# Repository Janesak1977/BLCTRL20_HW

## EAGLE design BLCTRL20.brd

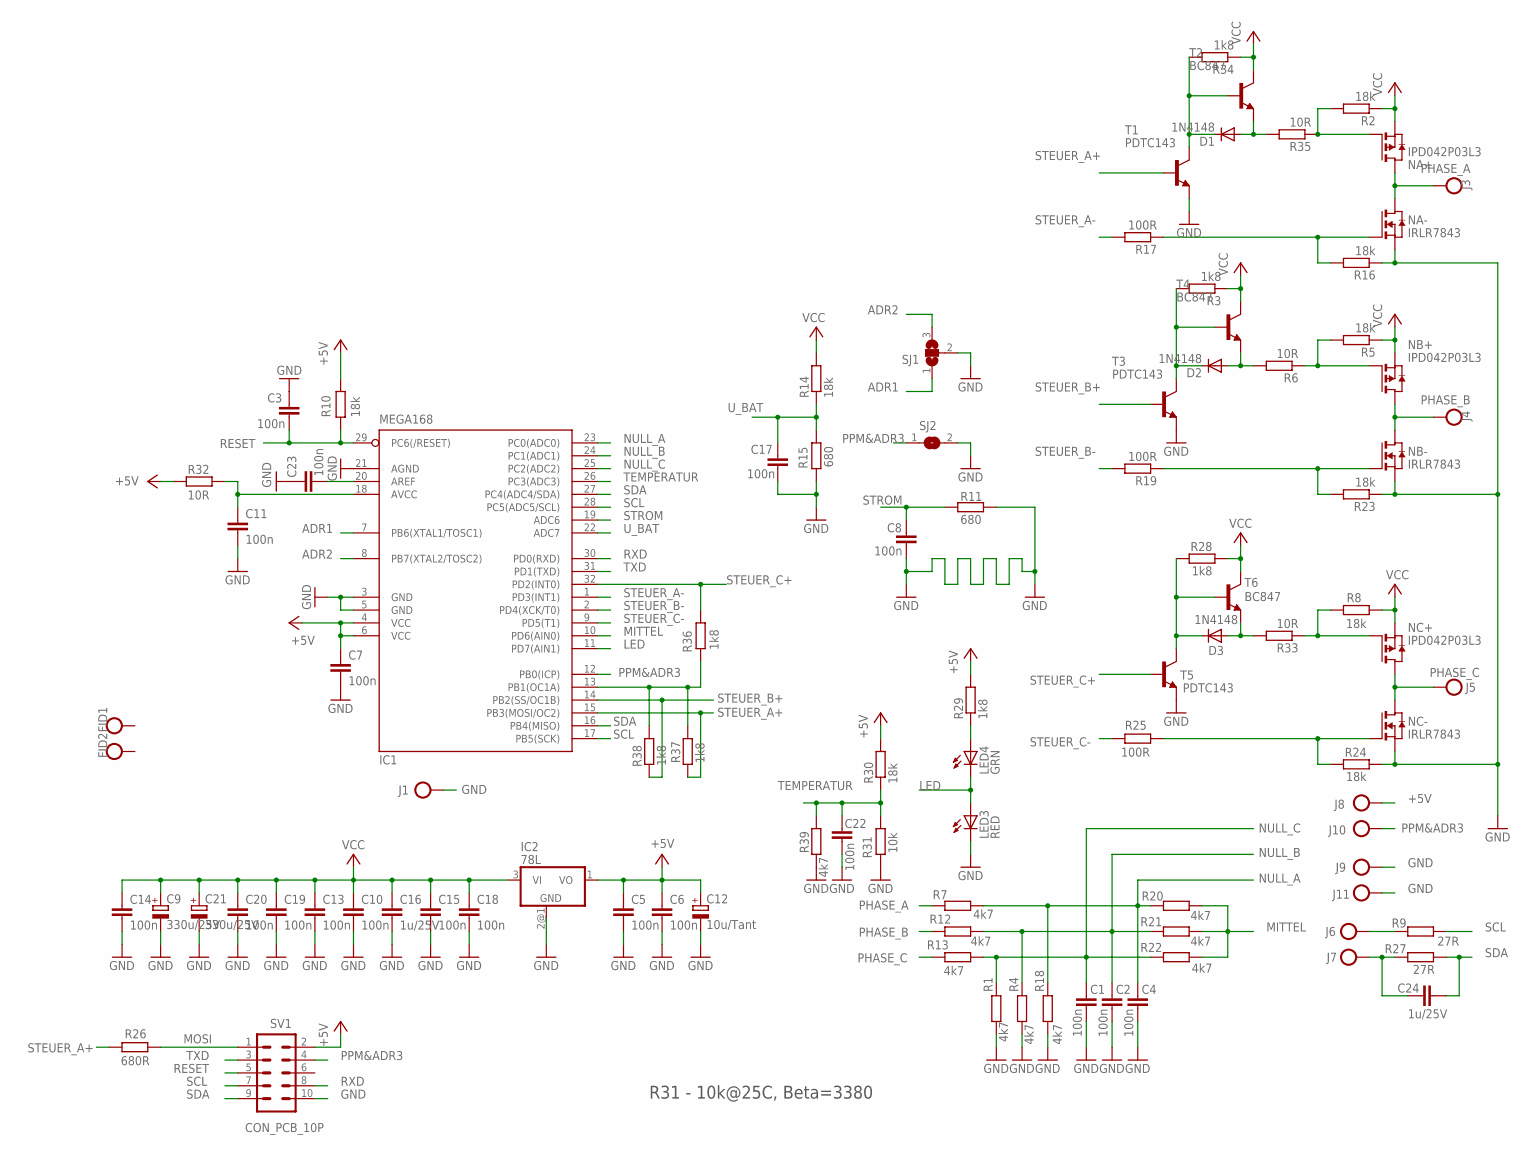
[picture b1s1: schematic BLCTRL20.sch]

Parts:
C1, C2, C3, C4, C5, C6, C7, C8, C10, C11, C13, C14, C15, C17, C18, C19, C20, C22, C23: 100n; C0603
C9, C21: 330u/25V; E2,5-5
C12: 10u/Tant; PANASONIC_B
C16, C24: 1u/25V; C0603
D1, D2, D3: 1N4148; SOD323-W
FID1, FID2: FIDUCIAL; FIDUCIAL_MARK
IC1: MEGA168; TQFP32-08
IC2: 78L; SOT89
J1, J3, J4, J5: SMDPAD40X20; PAD40X20
J6, J7: SE11
J8, J9, J10: SMDPAD25X25; PAD24X15
J11: SMDPAD24X12; PAD24X12
LED3: RED; CHIPLED_0603
LED4: GRN; CHIPLED_0603
NA+: IPD042P03L3; TO252
NA-: IRLR7843; TO252
NB+: IPD042P03L3; TO252
NB-: IRLR7843; TO252
NC+: IPD042P03L3; TO252
NC-: IRLR7843; TO252
R1, R4, R7, R12, R13, R18, R20, R21, R22, R39: 4k7; R0603
R2, R5, R8, R16, R23, R24: 18k; R0805
R3, R28, R29, R34, R36, R37, R38: 1k8; R0603
R6, R32, R33, R35: 10R; R0603
R9, R27: 27R; R0603
R10, R14, R30: 18k; R0603
R11, R15: 680; R0603
R17, R19, R25: 100R; R0603
R26: 680R; R0603
R31: 10k; R0603
SJ1: SJ2W; SJ_2
SJ2: SJ
SV1: CON_PCB_10P; BOARD_CON_SMD
T1, T3, T5: PDTC143; SC75_INFINEON
T2, T4, T6: BC847; SC75_INFINEON

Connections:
+5V: C5.1, C6.1, C7.1, C12.+, IC1.4 (VCC), IC1.6 (VCC), IC2.1 (VO), J8.P$1, R10.2, R29.2, R30.2, R32.2, SV1.2
ADR1: IC1.7 (PB6(XTAL1/TOSC1)), SJ1.1
ADR2: IC1.8 (PB7(XTAL2/TOSC2)), SJ1.3
GND: C1.2, C2.2, C3.1, C4.2, C5.2, C6.2, C7.2, C8.2, C9.-, C10.2, C11.2, C12.-, C13.2, C14.2, C15.2, C16.2, C17.2, C18.2, C19.2, C20.2, C21.-, C22.2, C23.1, IC1.3 (GND), IC1.5 (GND), IC1.21 (AGND), IC2.2@1 (GND), J1.P$1, J9.P$1, J11.P$1, LED3.C, NA-.3 (S), NB-.3 (S), NC-.3 (S), R1.1, R4.1, R11.1, R15.1, R16.1, R18.1, R23.1, R24.1, R31.1, R39.1, SJ1.2, SJ2.2, SV1.10, T1.2 (E), T3.2 (E), T5.2 (E)
LED: IC1.11 (PD7(AIN1)), LED3.A, LED4.C
MITTEL: IC1.10 (PD6(AIN0)), R20.1, R21.1, R22.1
MOSI: R26.1, SV1.1
unnamed: LED4.A, R29.1
unnamed: NA-.1 (G), R16.2, R17.1
unnamed: NA+.1 (G), R2.2, R35.1
unnamed: D1.A, R35.2, T2.2 (E)
unnamed: D1.C, R34.2, T1.3 (C), T2.1 (B)
unnamed: C24.2, J7.MP, R27.2
unnamed: J6.MP, R9.2
unnamed: NC-.1 (G), R24.2, R25.1
unnamed: NB-.1 (G), R19.1, R23.2
unnamed: NC+.1 (G), R8.2, R33.1
unnamed: NB+.1 (G), R5.2, R6.1
unnamed: D2.A, R6.2, T4.2 (E)
unnamed: D3.A, R33.2, T6.2 (E)
unnamed: D2.C, R3.2, T3.3 (C), T4.1 (B)
unnamed: D3.C, R28.2, T5.3 (C), T6.1 (B)
unnamed: IC1.13 (PB1(OC1A)), R36.1, R37.2, R38.2
unnamed: C23.2, IC1.20 (AREF)
unnamed: C11.1, IC1.18 (AVCC), R32.1
NULL_A: C4.1, IC1.23 (PC0(ADC0)), R7.1, R18.2, R20.2
NULL_B: C2.1, IC1.24 (PC1(ADC1)), R4.2, R12.1, R21.2
NULL_C: C1.1, IC1.25 (PC2(ADC2)), R1.2, R13.1, R22.2
PHASE_A: J3.P$1, NA+.2 (D), NA-.2 (D), R7.2
PHASE_B: J4.P$1, NB+.2 (D), NB-.2 (D), R12.2
PHASE_C: J5.P$1, NC+.2 (D), NC-.2 (D), R13.2
PPM&ADR3: IC1.12 (PB0(ICP)), J10.P$1, SJ2.1, SV1.4
RESET: C3.2, IC1.29 (PC6(/RESET)), R10.1, SV1.5
RXD: IC1.30 (PD0(RXD)), SV1.8
SCL: IC1.17 (PB5(SCK)), IC1.28 (PC5(ADC5/SCL)), R9.1, SV1.7
SDA: C24.1, IC1.16 (PB4(MISO)), IC1.27 (PC4(ADC4/SDA)), R27.1, SV1.9
STEUER_A+: IC1.15 (PB3(MOSI/OC2)), R26.2, R37.1, T1.1 (B)
STEUER_A-: IC1.1 (PD3(INT1)), R17.2
STEUER_B+: IC1.14 (PB2(SS/OC1B)), R38.1, T3.1 (B)
STEUER_B-: IC1.2 (PD4(XCK/T0)), R19.2
STEUER_C+: IC1.32 (PD2(INT0)), R36.2, T5.1 (B)
STEUER_C-: IC1.9 (PD5(T1)), R25.2
STROM: C8.1, IC1.19 (ADC6), R11.2
TEMPERATUR: C22.1, IC1.26 (PC3(ADC3)), R30.1, R31.2, R39.2
TXD: IC1.31 (PD1(TXD)), SV1.3
U_BAT: C17.1, IC1.22 (ADC7), R14.1, R15.2
VCC: C9.+, C10.1, C13.1, C14.1, C15.1, C16.1, C18.1, C19.1, C20.1, C21.+, IC2.3 (VI), NA+.3 (S), NB+.3 (S), NC+.3 (S), R2.1, R3.1, R5.1, R8.1, R14.2, R28.1, R34.1, T2.3 (C), T4.3 (C), T6.3 (C)

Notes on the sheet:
R31 - 10k@25C, Beta=3380

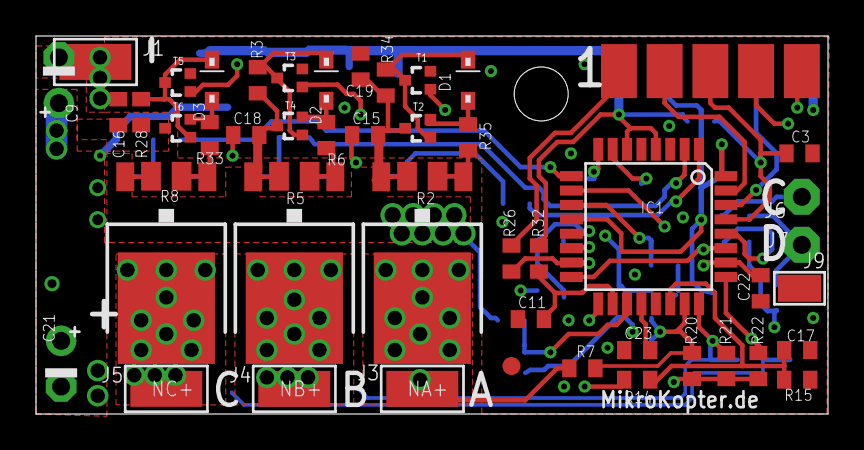
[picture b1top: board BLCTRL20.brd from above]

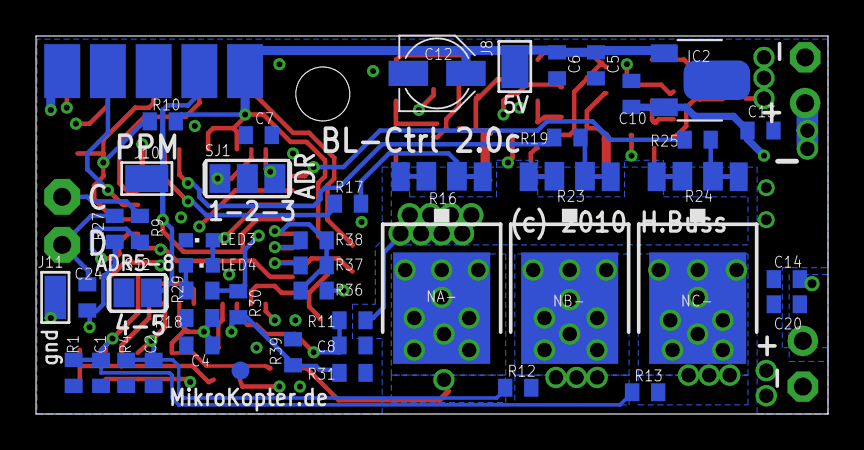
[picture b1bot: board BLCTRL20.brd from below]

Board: 4 copper layers, 44.0 x 21.0 mm, 97 parts (47 on the bottom side), 47 nets.

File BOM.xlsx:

Part | Value | Device | Package
R11 | 680 | R-EU_R0603 | R0603
R15 | 680 | R-EU_R0603 | R0603
C1 | 100n | C-EUC0603 | C0603
C10 | 100n | C-EUC0603 | C0603
C11 | 100n | C-EUC0603 | C0603
C13 | 100n | C-EUC0603 | C0603
C14 | 100n | C-EUC0603 | C0603
C15 | 100n | C-EUC0603 | C0603
C17 | 100n | C-EUC0603 | C0603
C18 | 100n | C-EUC0603 | C0603
C19 | 100n | C-EUC0603 | C0603
C2 | 100n | C-EUC0603 | C0603
C20 | 100n | C-EUC0603 | C0603
C22 | 100n | C-EUC0603 | C0603
C23 | 100n | C-EUC0603 | C0603
C3 | 100n | C-EUC0603 | C0603
C4 | 100n | C-EUC0603 | C0603
C5 | 100n | C-EUC0603 | C0603
C6 | 100n | C-EUC0603 | C0603
C7 | 100n | C-EUC0603 | C0603
C8 | 100n | C-EUC0603 | C0603
R17 | 100R | R-EU_R0603 | R0603
R19 | 100R | R-EU_R0603 | R0603
R25 | 100R | R-EU_R0603 | R0603
R32 | 10R | R-EU_R0603 | R0603
R33 | 10R | R-EU_R0603 | R0603
R35 | 10R | R-EU_R0603 | R0603
R6 | 10R | R-EU_R0603 | R0603
C12 | 10u/Tant | CPOL-EUB | PANASONIC_B
R10 | 18k | R-EU_R0603 | R0603
R14 | 18k | R-EU_R0603 | R0603
R16 | 18k | R-EU_R0805 | R0805
R2 | 18k | R-EU_R0805 | R0805
R23 | 18k | R-EU_R0805 | R0805
R24 | 18k | R-EU_R0805 | R0805
R30 | 18k | R-EU_R0603 | R0603
R5 | 18k | R-EU_R0805 | R0805
R8 | 18k | R-EU_R0805 | R0805
R28 | 1k8 | R-EU_R0603 | R0603
R29 | 1k8 | R-EU_R0603 | R0603
R3 | 1k8 | R-EU_R0603 | R0603
R34 | 1k8 | R-EU_R0603 | R0603
R36 | 1k8 | R-EU_R0603 | R0603
R37 | 1k8 | R-EU_R0603 | R0603
R38 | 1k8 | R-EU_R0603 | R0603
D1 | 1N4148 | DIODE-SOD323-W | SOD323-W
D2 | 1N4148 | DIODE-SOD323-W | SOD323-W
D3 | 1N4148 | DIODE-SOD323-W | SOD323-W
C16 | 1u/25V | C-EUC0603 | C0603
C24 | 1u/25V | C-EUC0603 | C0603
R27 | 27R | R-EU_R0603 | R0603
R9 | 27R | R-EU_R0603 | R0603
C21 | 330u/25V | CPOL-EUE2.5-5 | E2,5-5
C9 | 330u/25V | CPOL-EUE2.5-5 | E2,5-5
R1 | 4k7 | R-EU_R0603 | R0603
R12 | 4k7 | R-EU_R0603 | R0603
R13 | 4k7 | R-EU_R0603 | R0603
R18 | 4k7 | R-EU_R0603 | R0603
R20 | 4k7 | R-EU_R0603 | R0603
R21 | 4k7 | R-EU_R0603 | R0603
R22 | 4k7 | R-EU_R0603 | R0603
R39 | 4k7 | R-EU_R0603 | R0603
R4 | 4k7 | R-EU_R0603 | R0603
R7 | 4k7 | R-EU_R0603 | R0603
R26 | 680R | R-EU_R0603 | R0603
IC2 | 78L | 78L | SOT89
T2 | BC847 | BC847 | SC75_INFINEON
T4 | BC847 | BC847 | SC75_INFINEON
T6 | BC847 | BC847 | SC75_INFINEON
NA+ | IPD042P03L3 | IPD042P03L3 | TO252
NB+ | IPD042P03L3 | IPD042P03L3 | TO252
NC+ | IPD042P03L3 | IPD042P03L3 | TO252
NA- | IRLR7843 | IRLR7843 | TO252
NB- | IRLR7843 | IRLR7843 | TO252
NC- | IRLR7843 | IRLR7843 | TO252
LED3 | LEDCHIPLED_0603 | CHIPLED_0603 | led
LED4 | LEDCHIPLED_0603 | CHIPLED_0603 | led
IC1 | MEGA168 | MEGA168 | TQFP32-08
T1 | PDTC143 | PDTC143 | SC75_INFINEON
T3 | PDTC143 | PDTC143 | SC75_INFINEON
T5 | PDTC143 | PDTC143 | SC75_INFINEON
R31 | PTC | R0603 | blctrl20

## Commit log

2015-01-02 Original

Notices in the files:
BLCTRL20.brd:
(c) 2010 H.Buss
